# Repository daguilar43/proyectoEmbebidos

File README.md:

# Proyecto Sistemas Embebidos
#

Aquí pueden encontrarse todos los archivos del proyecto Amiplanta realizado para la materia Sistemas Embebidos durante el semestre 2022-2 en la Universidad Nacional de Colombia.
Dentro de estas carpetas pueden encontrarse:

*Proyecto en Kicad con el esquemático del dispositivo, huellas de los los diferentes componentes y layout de la PCB que fue enviada a producción con sus 
respectivas reglas de diseño + Logo del proyecto en la máscara de la PCB.

*Huellas realizadas manualmente de alunos componentes (utilizados para el diseño de la PCB).

*Código final desarrollado con ayuda de RIOT OS y el sdk para la Esp32-Wroom32, placa que fue utilizada para el montaje del proyecto.

*Modelo 3D utilizado para la matera.

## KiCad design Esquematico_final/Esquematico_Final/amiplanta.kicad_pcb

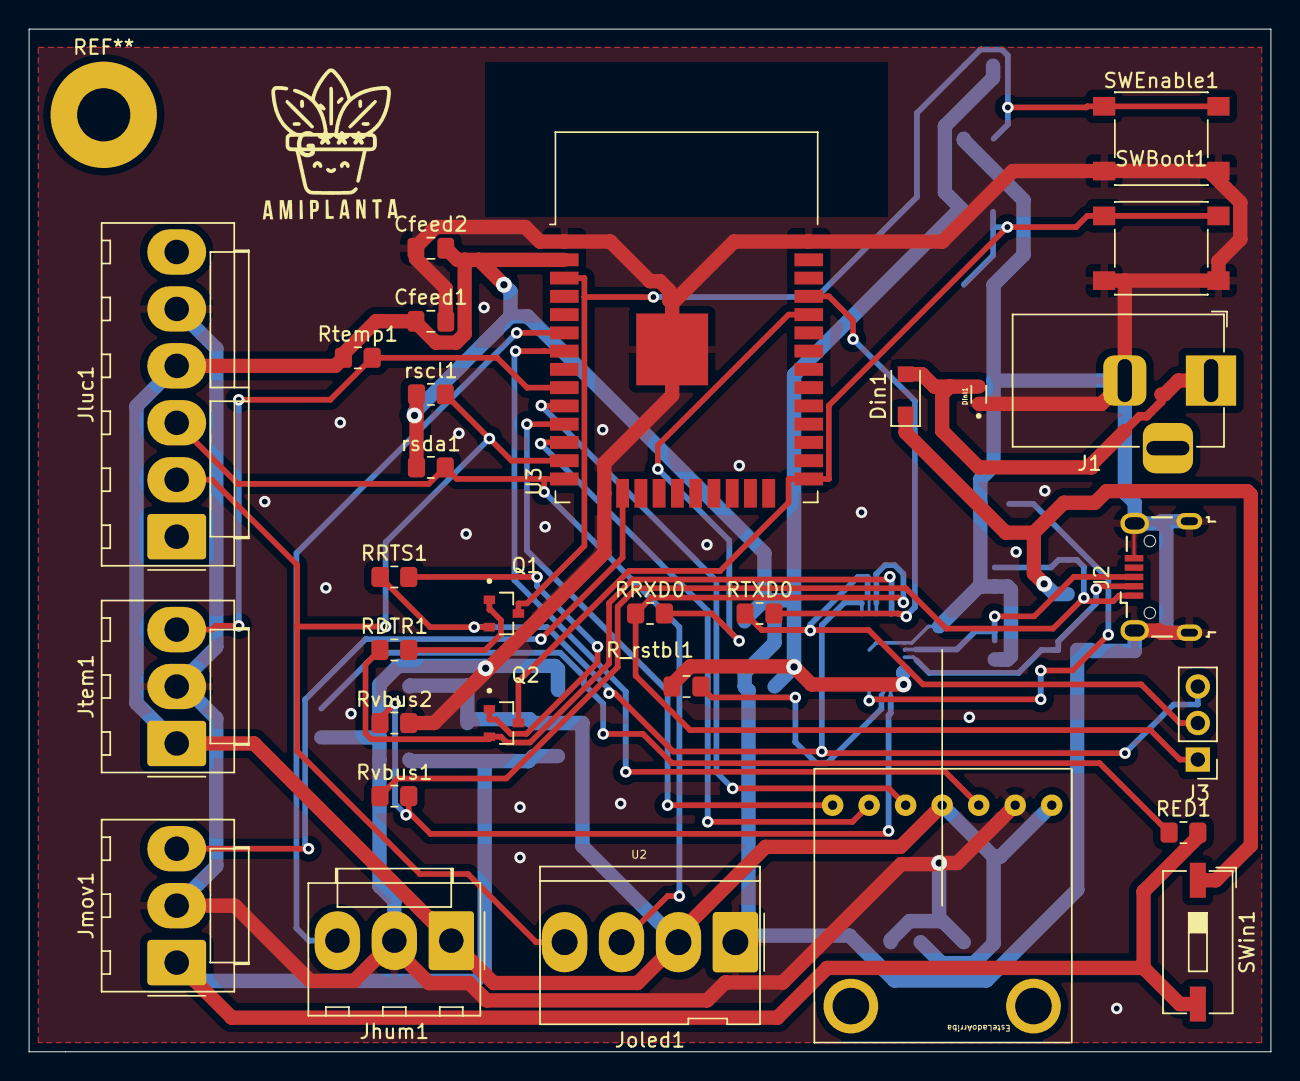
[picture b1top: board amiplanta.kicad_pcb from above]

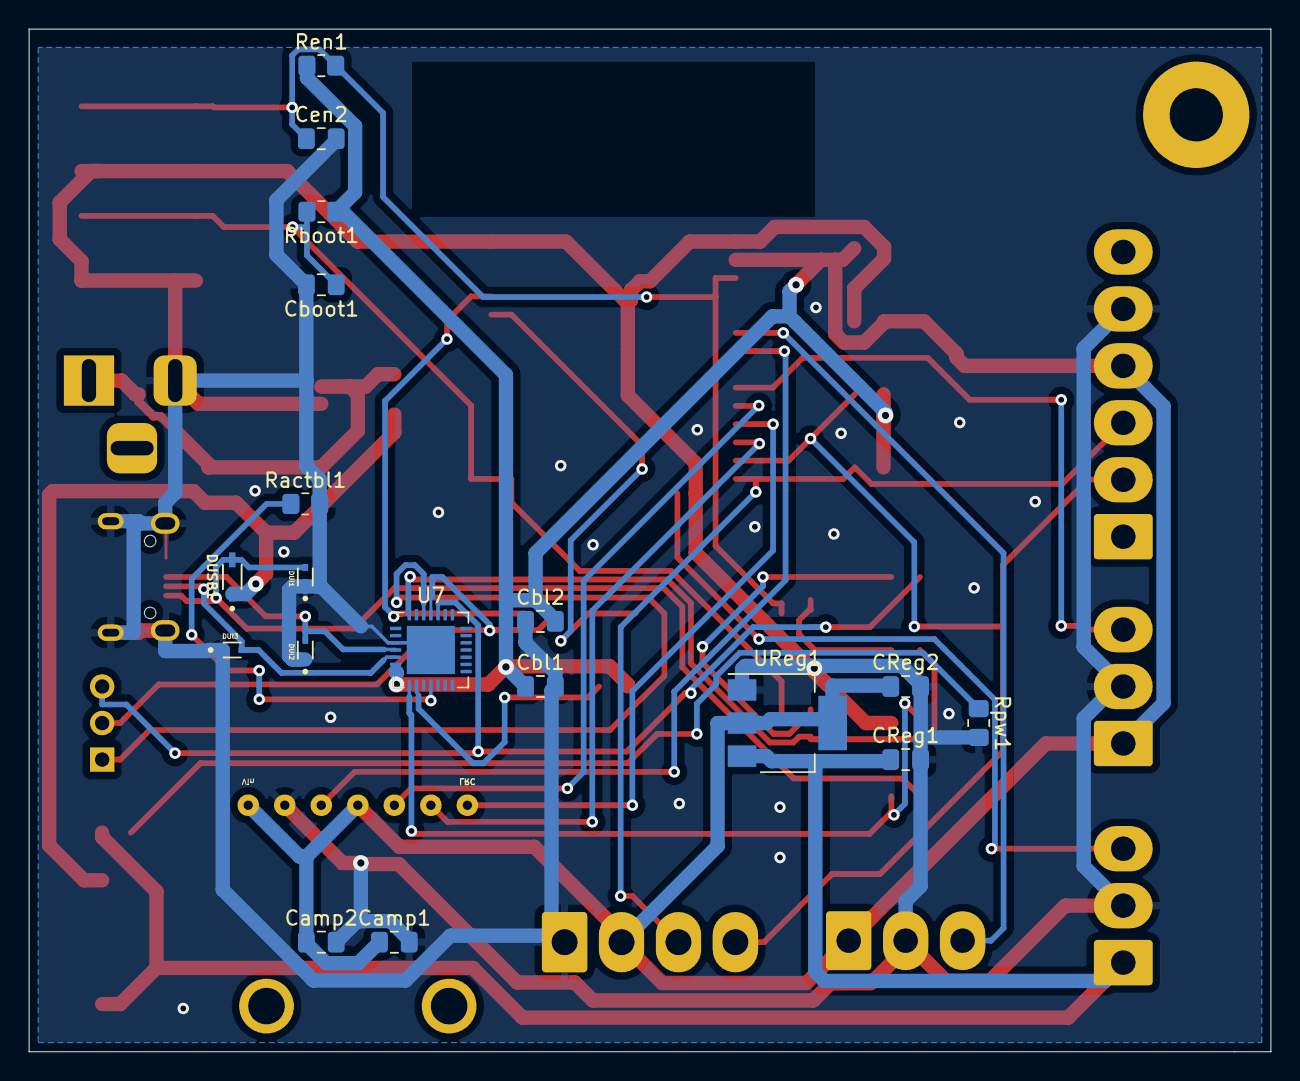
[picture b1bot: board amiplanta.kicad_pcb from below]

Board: 2 copper layers, 86.4 x 71.1 mm, 48 parts (18 on the bottom side), 31 nets.

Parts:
CReg1, CReg2: 1u; C_0805_2012Metric_Pad1.18x1.45mm_HandSolder
Camp1: 10u; C_0805_2012Metric_Pad1.18x1.45mm_HandSolder
Camp2: 0.1u; C_0805_2012Metric_Pad1.18x1.45mm_HandSolder
Cbl1: 0.1uF/50V(10%); C_0805_2012Metric_Pad1.18x1.45mm_HandSolder
Cbl2: 4.7uF/6.3V(10%); C_0805_2012Metric_Pad1.18x1.45mm_HandSolder
Cboot1: 0.1uF/50V(10%)(NC); C_0805_2012Metric_Pad1.18x1.45mm_HandSolder
Cen2: 0.1uF/50V(10%)(NC); C_0805_2012Metric_Pad1.18x1.45mm_HandSolder
Cfeed1: 22uF/10V(20%); C_0805_2012Metric_Pad1.18x1.45mm_HandSolder
Cfeed2: 0.1uF/50(10%); C_0805_2012Metric_Pad1.18x1.45mm_HandSolder
DUSB1: BAT760-7; SOD2513X120N
DUl1, DUl2, DUl3: LESD5D5.0CT1G; TVS_LESD5D5.0CT1G
Din1: MBR1020VL; D_SOD-123F
Dinl1: LESD5D5.0CT1G; TVS_LESD5D5.0CT1G
J1: Jack-DC; BarrelJack_Horizontal
J2: USB_B_Micro; USB_Micro-B_Wuerth_629105150521
J3: Conn_01x03_Female; PinHeader_1x03_P2.54mm_Vertical
Jhum1: Conn_01x03_Female; Molex_KK-396_A-41791-0003_1x03_P3.96mm_Vertical
Jluc1: Conn_01x06_Female; Molex_KK-396_A-41791-0006_1x06_P3.96mm_Vertical
Jmov1: Conn_01x03_Female; Molex_KK-396_A-41791-0003_1x03_P3.96mm_Vertical
Joled1: Conn_01x04_Female; Molex_KK-396_5273-04A_1x04_P3.96mm_Vertical
Jtem1: Conn_01x03_Female; Molex_KK-396_A-41791-0003_1x03_P3.96mm_Vertical
Q1, Q2: SS8050-G; TRANS_SS8050-G
RDTR1: 10K(5%); R_0805_2012Metric_Pad1.20x1.40mm_HandSolder
RED1: LED; R_0805_2012Metric_Pad1.20x1.40mm_HandSolder
RRTS1: 10K(5%); R_0805_2012Metric_Pad1.20x1.40mm_HandSolder
RRXD0: 0R(5%); R_0805_2012Metric_Pad1.20x1.40mm_HandSolder
RTXD0: 0R(5%); R_0805_2012Metric_Pad1.20x1.40mm_HandSolder
R_rstbl1: 2k(5%); R_0805_2012Metric_Pad1.20x1.40mm_HandSolder
Ractbl1: 10k(5%); R_0805_2012Metric_Pad1.20x1.40mm_HandSolder
Rboot1: 10K(5%); R_0805_2012Metric_Pad1.20x1.40mm_HandSolder
Ren1: 10K(5%); R_0805_2012Metric_Pad1.20x1.40mm_HandSolder
Rpw1: 1k; R_0805_2012Metric_Pad1.20x1.40mm_HandSolder
Rtemp1: 4,7k; R_0805_2012Metric_Pad1.20x1.40mm_HandSolder
Rvbus1: 22.1K(5%); R_0805_2012Metric_Pad1.20x1.40mm_HandSolder
Rvbus2: 47.5K(5%); R_0805_2012Metric_Pad1.20x1.40mm_HandSolder
SWBoot1: SW_Push; SW_Push_1P1T_NO_6x6mm_H9.5mm
SWEnable1: SW_Push; SW_Push_1P1T_NO_6x6mm_H9.5mm
SWin1: SW_DIP_x01; SW_DIP_SPSTx01_Slide_9.78x4.72mm_W8.61mm_P2.54mm
U2: MAX98357AETE+; MAX98357A_ModuloEditado
U3: ESP32-WROOM-32
U7: CP2102N-Axx-xQFN28; QFN-28-1EP_5x5mm_P0.5mm_EP3.35x3.35mm
UReg1: AMS1117-3.3; SOT-223-3_TabPin2
rscl1: 4.7k; R_0805_2012Metric_Pad1.20x1.40mm_HandSolder
rsda1: 4.7k; R_0805_2012Metric_Pad1.20x1.40mm_HandSolder

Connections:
+3.3V: CReg2.1, Camp1.1, Camp2.1, Cbl1.1, Cbl2.2, Cfeed1.1, Cfeed2.2, Jhum1.1, Jluc1.4, Joled1.2, Jtem1.1, R_rstbl1.1, Rboot1.1, Ren1.1, Rtemp1.1, U2.1 (VDD), U2.4 (GAIN_SLOT), U3.2 (VDD), U7.6 (VDD), U7.7 (VREGIN), UReg1.2 (VO), rscl1.1, rsda1.1
+5V: CReg1.1, Jmov1.1, RED1.2 (A), SWin1.2, UReg1.3 (VI)
+5V_Jack: DUSB1.C, Din1.1 (K), SWin1.1
/CP2102N-A02-GQFN28(Bootloader)/DTR: Q2.2, RDTR1.1, U7.28 (~DTR)
/CP2102N-A02-GQFN28(Bootloader)/RTS: J3.3, Q1.2, RRTS1.1, U7.24 (~RTS)
/CP2102N-A02-GQFN28(Bootloader)/RXD: J3.2, RTXD0.1, U7.25 (RXD)
/CP2102N-A02-GQFN28(Bootloader)/RXD0: RRXD0.2, U3.34 (RXD0/IO3)
/CP2102N-A02-GQFN28(Bootloader)/TXD: J3.1, RRXD0.1, U7.26 (TXD)
/CP2102N-A02-GQFN28(Bootloader)/TXD0: RTXD0.2, U3.35 (TXD0/IO1)
/CP2102N-A02-GQFN28(Bootloader)/USB_DN: DUl3.2, J2.2 (D-), U7.5 (D-)
/CP2102N-A02-GQFN28(Bootloader)/USB_DP: DUl2.2, J2.3 (D+), U7.4 (D+)
/CP2102N-A02-GQFN28(Bootloader)/VBUS: DUSB1.A, DUl1.2, J2.1 (VBUS), Rvbus1.1
/ESP32/Amp_Din: U2.5 (DIN), U3.10 (IO25)
/ESP32/BCLK: U2.6 (BCLK), U3.12 (IO27)
/ESP32/LRC: U2.7 (LRCLK), U3.11 (IO26)
/ESP32/SCL: Jluc1.2, Joled1.4, U3.13 (IO14), rscl1.2
/ESP32/SDA: Jluc1.3, Joled1.3, U3.14 (IO12), rsda1.2
/ESP32/amp_D_mode: U2.3 (~SD_MODE), U3.7 (IO35)
/Sensores/dh: Jhum1.3, U3.6 (IO34)
/Sensores/dm: Jmov1.3, U3.16 (IO13)
/Sensores/dt: Jtem1.3, Rtemp1.2, U3.9 (IO33)
BOOT: Cboot1.1, Q2.3, Rboot1.2, SWBoot1.1, U3.25 (IO0)
EN: Cen2.1, Q1.3, Ren1.2, SWEnable1.1, U3.3 (EN)
GNDREF: CReg1.2, CReg2.2, Camp1.2, Camp2.2, Cbl1.2, Cbl2.1, Cboot1.2, Cen2.2, Cfeed1.2, Cfeed2.1, DUl1.1, DUl2.1, DUl3.1, Dinl1.1, J1.2, J2.5 (GND), J2.6 (Shield), Jhum1.2, Jluc1.5, Jmov1.2, Joled1.1, Jtem1.2, Ractbl1.2, Rpw1.2, Rvbus2.2, SWBoot1.2, SWEnable1.2, U2.2 (GND), U3.1 (GND), U3.15 (GND), U3.38 (GND), U3.39 (GND), U7.3 (GND), U7.29 (GND), UReg1.1 (GND)
unnamed: Din1.2 (A), Dinl1.2, J1.1
unnamed: Q1.1, RDTR1.2
unnamed: Q2.1, RRTS1.2
unnamed: RED1.1 (K), Rpw1.1
unnamed: R_rstbl1.2, U7.9 (~RST)
unnamed: Ractbl1.1, U7.11 (~SUSPEND)
unnamed: Rvbus1.2, Rvbus2.1, U7.8 (VBUS)

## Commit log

2022-09-27 Add files via upload
    Primer avance esquematico
2022-10-06 Esquemáticos tentativos de Bootloader, Conexión USB y Potencia. Revisar valores de los componentes, especialmente Capacitores
2022-10-06 Esquematicos sin error en texto plano
2022-10-06 intento push
2022-10-06 Circuito Pantalla Oled SSD1306 implementado. Modelo y Footprints SD1306 agregados
2022-10-06 Agregado circuito de potencia a través de Jack y selector de posición para alimentar de USB, Jack o apagar
2022-10-10 sensores 1
2022-10-11 Conexion Sensores
2022-10-15 actualizacion huellas resitencias y capacitorees
2022-10-15 Huellas asignadas. Revisar si algunos de los módulos serán cambiados por conectores Molex.
2022-10-20 Desarrollo PCB
2022-10-25 Correciones Finales Esquemático - Revisar error con huella del Amplificador de Sonido
2022-10-25 PCB organizada para autoruteo
2022-10-25 PCB Final
2022-10-26 Placa diseño Final para imprimir
2022-11-01 Esquematico final y ejemplos riot
2022-11-23 Oled Con logo Amiplanta (instrucciones en README sd1306_i2c
2022-12-07 Final Final, no va mas
2022-12-07 Add files via upload
    PDF esquematico
2022-12-07 Create Diseño3D
2022-12-07 Add files via upload
    Diseño 3D final
